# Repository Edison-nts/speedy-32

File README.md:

# speedy-32

Speeduino Hardware - STM32

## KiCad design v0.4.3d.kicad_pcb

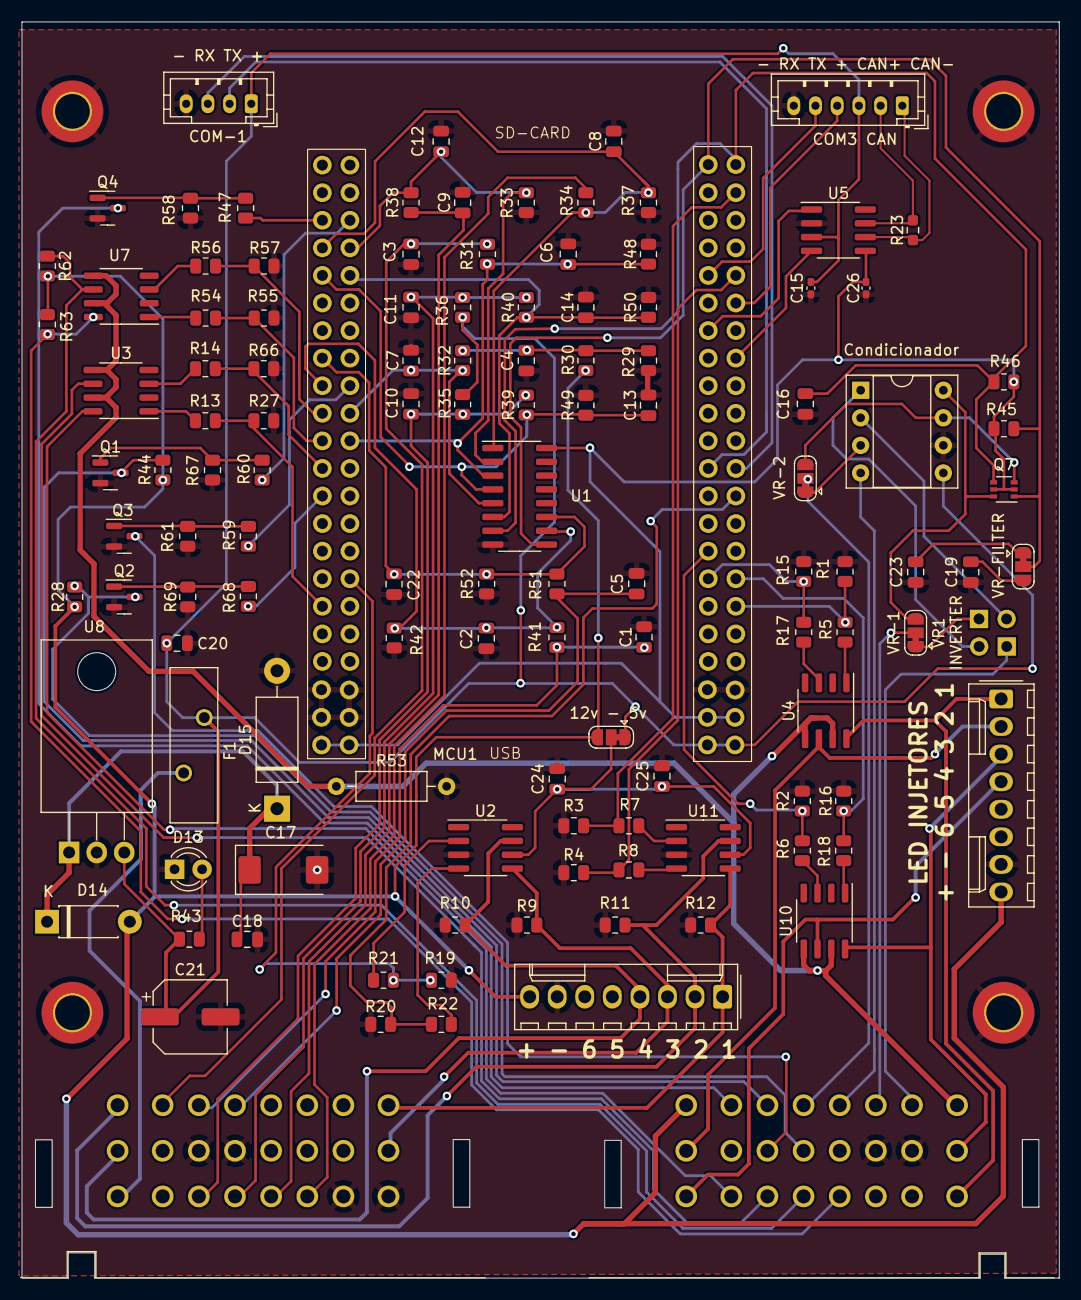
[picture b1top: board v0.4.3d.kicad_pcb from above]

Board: 2 copper layers, 95.6 x 115.7 mm, 126 parts (0 on the bottom side), 95 nets.

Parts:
C1, C3, C4, C5, C9, C10, C11, C16, C18, C20, C24: 0.1uF; C_0805_2012Metric
C2, C6, C7, C12, C13, C14, C22: 0.22uF; C_0805_2012Metric
C8: 470pf; C_0805_2012Metric
C15, C26: 100n; C_0402_1005Metric_Pad0.74x0.62mm_HandSolder
C17: 10uF; CP_EIA-7343-31_Kemet-D
C19: 0.01uF; C_0805_2012Metric
C21: 47uF; CP_Elec_6.3x5.4
C23: 4700pF; C_0805_2012Metric
C25: 1uF; C_0805_2012Metric
D13: LED; LED_D3.0mm
D14: SB230TA; D_DO-41_SOD81_P7.62mm_Horizontal
D15: D_TVS; D_DO-15_P12.70mm_Horizontal
F1: Polyfuse; Fuse_BelFuse_0ZRE0055FF_L14.0mm_W4.1mm
H1, H2, H3, H4: MountingHole_Pad; MountingHole_3.2mm_M3_ISO7380_Pad_TopBottom
IC3: Condicionador; DIP-8_W7.62mm_Socket
J1: LED INJETORES; Molex_KK-254_AE-6410-08A_1x08_P2.54mm_Vertical
J4: COM-1; JST_PH_B4B-PH-K_1x04_P2.00mm_Vertical
J5: COM3 CAN; JST_PH_B6B-PH-K_1x06_P2.00mm_Vertical
J6: CONN_BLACK; Delphi_Sicma_24_Grey
J7: CONN_GREY; Delphi_Sicma_24_Black
J8: LED IGNICAO; Molex_KK-254_AE-6410-08A_1x08_P2.54mm_Vertical
JP1: 12v - 5v; SolderJumper-3_P1.3mm_Bridged12_RoundedPad1.0x1.5mm
JP2: VR-1; SolderJumper-3_P1.3mm_Bridged12_RoundedPad1.0x1.5mm
JP3: VR-2; SolderJumper-3_P1.3mm_Bridged12_RoundedPad1.0x1.5mm
JP4: VR-FILTER; SolderJumper-3_P1.3mm_Bridged12_RoundedPad1.0x1.5mm
JP5: VR1-JP-PLUS; PinHeader_1x02
JP6: VR1-JP-MINUS; PinHeader_1x02
MCU1: MCU-STM32-DEVEBOX-SHIELD; Stm32_devebox_shield_Pin_Only
Q1, Q2, Q3, Q4: 2N7002; SOT-23
Q7: PMGD280UN; SOT-363_SC-70-6
R1, R2, R3, R4, R15, R16, R19, R20, R27, R55, R57, R58, R61, R66, R67, R69: 100k; R_0805_2012Metric
R5, R6, R7, R8, R13, R14, R17, R18, R21, R22, R45, R46, R47, R54, R56, R59, R60, R68: 1k; R_0805_2012Metric
R9, R10, R11, R12, R28, R44, R62, R63: 10k; R_0805_2012Metric
R23: 120; R_0603_1608Metric_Pad0.98x0.95mm_HandSolder
R29, R43: 1.5K; R_0805_2012Metric
R30: 10K; R_0805_2012Metric
R31, R34, R38, R39, R40, R41, R51: 47K; R_0805_2012Metric
R32: 470R; R_0805_2012Metric
R33, R37, R42, R48, R49, R50, R52: 100K; R_0805_2012Metric
R35, R36: 5.1K; R_0805_2012Metric
R53: 47R; R_Axial_DIN0207_L6.3mm_D2.5mm_P10.16mm_Horizontal
U1: SP720; SOIC-16_3.9x9.9mm_P1.27mm
U2, U11: TC4424A; SOIC-8_3.9x4.9mm_P1.27mm
U3, U4, U7, U10: VNLD5090; SO-8_3.9x4.9mm_P1.27mm
U5: TJA1051T-3; SOIC-8_3.9x4.9mm_P1.27mm
U8: LM2940S-5.0; TO-220-3_Horizontal_TabDown

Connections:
12V-SW: D14.2 (A), J1.8, J6.A8, J8.8, JP1.3 (B), R28.2, R30.2, R44.2, R62.2, R63.2
+3V3: C26.2, MCU1.3V3-1 (3V3), MCU1.3V3-2 (3V3), MCU1.3V3-3 (3V3), MCU1.3V3-4 (3V3), Q7.2 (G), Q7.5 (G), R45.2, R46.1, U1.16 (V+), U5.5 (VIO)
+5V: C15.1, C20.1, C21.1, F1.2, IC3.5, J4.1, J5.3, JP1.1 (A), MCU1.5V-1 (5V), MCU1.5V-2 (5V), R35.2, R36.2, R43.2, U5.3 (VCC), U8.3 (VO)
+5VA: F1.1, J7.C8
ADC-Clamp-1: C8.1, MCU1.PC0 (MAP), R34.1, R37.1, U1.1 (I1)
ADC-Clamp-2: C12.1, MCU1.PC1 (TPS), R33.1, R38.1, U1.2 (I2)
ADC-Clamp-3: C6.1, MCU1.PB1 (O2), R31.1, R48.1, U1.3 (I3)
ADC-Clamp-4: C13.1, MCU1.PC2 (IAT), R39.1, R49.1, U1.4 (I4)
ADC-Clamp-5: C7.1, MCU1.PC5 (BAT), R32.1, U1.5 (I5)
ADC-Clamp-6: C14.1, MCU1.PC3 (CLT), R40.1, R50.1, U1.6 (I6)
ADC-Clamp-7: C16.2, MCU1.PE1 (TRG-2), Q7.4 (S), R46.2, U1.7 (I7)
ADC-Clamp-8: JP4.2 (C), MCU1.PE0 (TRG-1), Q7.1 (S), R45.1, U1.9 (I8)
ADC-Clamp-9: C2.1, MCU1.PA6, R41.1, R42.1, U1.10 (I9)
ADC-Clamp-10: C22.1, MCU1.PA4, R51.1, R52.1, U1.11 (I10)
BOOST-OUT: J6.C6, U3.6 (DRAIN2)
CAN+: J5.2, R23.2, U5.7 (CANH)
CAN-: J5.1, R23.1, U5.6 (CANL)
CLT_Sensor: C11.1, J7.C5, R36.1, R40.2
COM1-RX: J4.3, MCU1.PA10 (RX1)
COM1-TX: J4.2, MCU1.PA9 (TX1)
COM3-RX: J5.5, MCU1.PD6
COM3-TX: J5.4, MCU1.PD5
FAN-OUT: J6.A7, Q4.3 (D)
FUELPUMP-OUT: J6.B6, Q3.3 (D)
GND: C1.2, C2.2, C3.2, C4.2, C5.2, C6.2, C7.2, C8.2, C9.2, C10.2, C11.2, C12.2, C13.2, C14.2, C15.2, C16.1, C17.2, C18.2, C19.1, C20.2, C21.2, C22.2, C23.2, C24.1, C25.1, C26.1, D13.1 (K), D15.2 (A), H1.1, H2.1, H3.1, H4.1, IC3.6, J1.7, J4.4, J5.6, J6.B2, J6.B3, J7.B5, J7.B6, J7.C1, J7.C2, J8.7, MCU1.GND1 (GND), MCU1.GND2 (GND), MCU1.GND3 (GND), MCU1.GND4 (GND), MCU1.GND5 (GND), MCU1.GND6 (GND), Q1.2 (S), Q2.2 (S), Q3.2 (S), Q4.2 (S), R1.2, R2.2, R3.2, R4.1, R9.2, R10.1, R11.1, R12.2, R15.2, R16.1, R19.2, R20.1, R27.2, R29.1, R33.2, R37.2, R42.2, R48.2, R49.2, R50.2, R52.2, R53.2, R55.2, R57.2, R58.2, R61.2, R66.2, R67.2, R69.2, U1.8 (GND), U2.3 (GND), U5.2 (GND), U8.2 (GND), U11.3 (GND)
GNDPWR: J6.A1, R53.1, U3.5 (SOURCE2), U3.7 (SOURCE1), U4.5 (SOURCE2), U4.7 (SOURCE1), U7.5 (SOURCE2), U7.7 (SOURCE1), U10.5 (SOURCE2), U10.7 (SOURCE1)
IAT_Sensor: C10.1, J7.C6, R35.1, R39.2
IDLE-OUT: J6.C7, U3.8 (DRAIN1)
IGN-1-OUT: J7.A1, J8.1, R12.1, U11.5 (OUT_B)
IGN-2-OUT: J7.A8, J8.2, R11.2, U11.7 (OUT_A)
IGN-3-OUT: J7.B1, J8.3, R9.1, U2.5 (OUT_B)
IGN-4-OUT: J7.B8, J8.4, R10.2, U2.7 (OUT_A)
IN-1: C1.1, J7.A6, R41.2
IN-2: C5.1, J7.A5, R51.2
INJ-1-OUT: J1.1, J6.C1, U4.8 (DRAIN1)
INJ-2-OUT: J1.2, J6.B8, U4.6 (DRAIN2)
INJ-3-OUT: J1.3, J6.B1, U10.8 (DRAIN1)
INJ-4-OUT: J1.4, J6.C8, U10.6 (DRAIN2)
MAP-EXT: J7.C3, R34.2
MCU-BOOST: MCU1.PE7, R14.2, R66.1
MCU-CAN-RX: MCU1.PD1, U5.4 (RXD)
MCU-CAN-TX: MCU1.PD2, U5.1 (TXD)
MCU-FAN: MCU1.PE6 (FAN), R47.2
MCU-IDLE-1: MCU1.PB11 (IDLE-1), R13.2, R27.1
MCU-IGN-1: MCU1.PD7 (COIL-1), R4.2, R8.2
MCU-IGN-2: MCU1.PB9 (COIL-2), R3.1, R7.2
MCU-IGN-3: MCU1.PA8 (COIL-3), R20.2, R22.2
MCU-IGN-4: MCU1.PB10 (COIL-4), R19.1, R21.2
MCU-INJ-1: MCU1.PD12 (INJ-1), R1.1, R5.2
MCU-INJ-2: MCU1.PD13 (INJ-2), R15.1, R17.2
MCU-INJ-3: MCU1.PD14 (INJ-3), R16.2, R18.2
MCU-INJ-4: MCU1.PD15 (INJ-4), R2.1, R6.2
MCU-OUT-1: MCU1.PC4, R56.2, R57.1
MCU-OUT-2: MCU1.PB0, R54.2, R55.1
MCU-OUT-3: MCU1.PE9, R68.2
MCU-PUMP: MCU1.PA7 (PUMP), R59.2
MCU-TACHO: MCU1.PC13 (TACH-OUT), R60.2
unnamed: C4.1, R29.2, R30.1, R32.2
unnamed: D13.2 (A), R43.1
unnamed: IC3.1, JP6.2 (B)
unnamed: IC3.2, JP5.2 (B)
unnamed: IC3.3, JP3.1 (A)
unnamed: IC3.7, JP3.3 (B), Q7.3 (D)
unnamed: IC3.8, JP2.3 (B), Q7.6 (D)
unnamed: JP2.1 (A), JP5.1 (A)
unnamed: C23.1, JP4.1 (A)
unnamed: C19.2, JP4.3 (B)
unnamed: Q1.1 (G), R60.1, R67.1
unnamed: Q2.1 (G), R68.1, R69.1
unnamed: Q3.1 (G), R59.1, R61.1
unnamed: Q4.1 (G), R47.1, R58.1
unnamed: R21.1, U2.2 (IN_A)
unnamed: R22.1, U2.4 (IN_B)
unnamed: R13.1, U3.1 (IN1)
unnamed: R14.1, U3.3 (IN2)
unnamed: R5.1, U4.1 (IN1)
unnamed: R17.1, U4.3 (IN2)
unnamed: R54.1, U7.1 (IN1)
unnamed: R56.1, U7.3 (IN2)
unnamed: R18.1, U10.1 (IN1)
unnamed: R6.1, U10.3 (IN2)
unnamed: R7.1, U11.2 (IN_A)
unnamed: R8.1, U11.4 (IN_B)
O2_Sensor: C3.1, J7.A7, R31.2
OUT-1: J6.C5, R62.1, U7.6 (DRAIN2)
OUT-2: J6.C4, R63.1, U7.8 (DRAIN1)
OUT-3: J6.B5, Q2.3 (D), R28.1
TACHO-OUT: J6.A6, Q1.3 (D), R44.1
TPS_Sensor: C9.1, J7.C4, R38.2
VR1+: J6.A3, JP2.2 (C)
VR1-: J6.A2, JP6.1 (A)
VR2+: J6.A5, JP3.2 (C)
VR2-: IC3.4, J6.A4
VRegIn: C17.1, C18.1, D14.1 (K), D15.1 (K), U8.1 (VI)
Vdrive: C24.2, C25.2, JP1.2 (C), U2.6 (VDD), U11.6 (VDD)

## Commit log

2024-11-25 commit inicial
